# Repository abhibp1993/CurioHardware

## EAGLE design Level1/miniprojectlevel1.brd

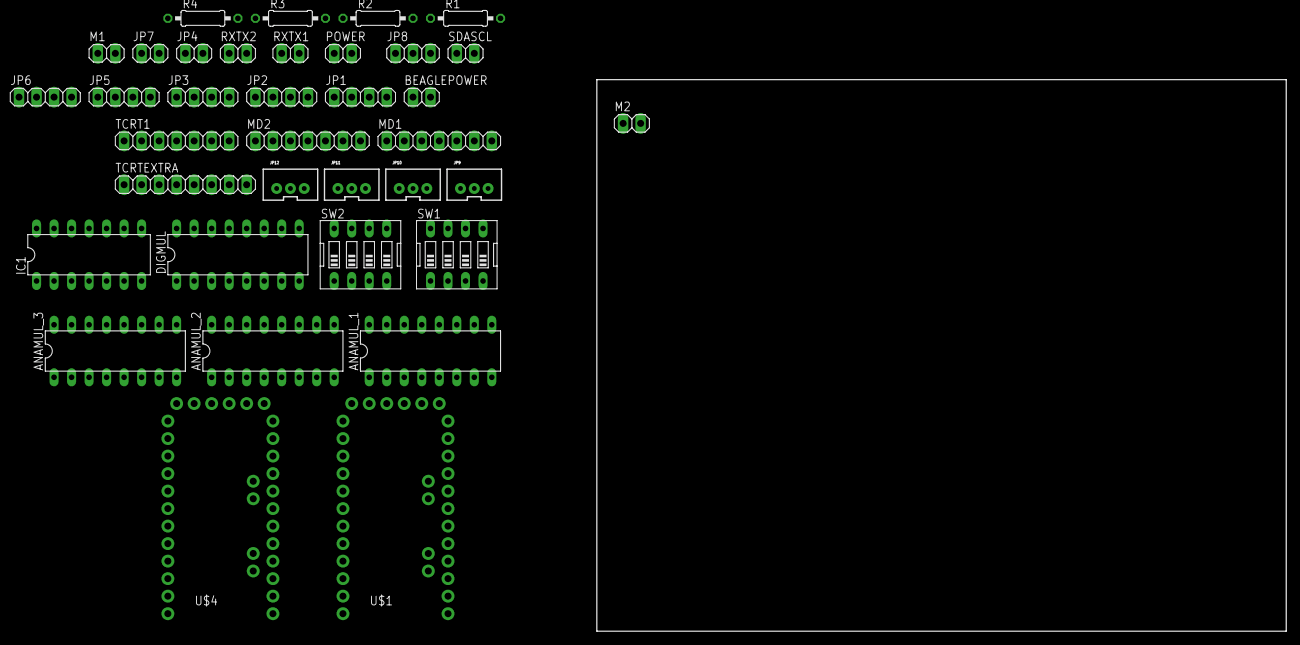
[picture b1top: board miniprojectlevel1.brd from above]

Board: 2 copper layers, 100.0 x 80.0 mm, 36 parts (0 on the bottom side), 64 nets, no tracks yet.

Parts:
ANAMUL_1, ANAMUL_2, ANAMUL_3: 4051N; DIL16
BEAGLEPOWER: 1X02
DIGMUL: 74ACT151N; DIL16
IC1: LM324N; DIL14
JP1, JP2, JP3, JP5, JP6: 1X04
JP4, JP7: 1X02
JP8: 1X03
JP9, JP10, JP11, JP12: JST-3-PTH-VERT
M1, M2: 1X02
MD1, MD2: 1X07
POWER: 1X02
R1, R2, R3, R4: 0207/10
RXTX1, RXTX2: 1X02
SDASCL: 1X02
SW1, SW2: EDG-04
TCRT1: 1X07
TCRTEXTRA: 1X08
U$1, U$4: ARDUINO_PRO_MINI

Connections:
GND: ANAMUL_1.8, ANAMUL_2.8, ANAMUL_3.8, DIGMUL.8
unnamed: DIGMUL.5, U$4.6
unnamed: ANAMUL_1.1, TCRT1.5
unnamed: ANAMUL_1.13, TCRT1.1
unnamed: ANAMUL_1.14, TCRT1.2
unnamed: ANAMUL_1.15, TCRT1.3
unnamed: ANAMUL_1.12, TCRT1.4
unnamed: ANAMUL_1.5, TCRT1.6
unnamed: ANAMUL_1.2, TCRT1.7
unnamed: DIGMUL.2, MD2.3
unnamed: M2.1, U$4.11
unnamed: DIGMUL.4, MD1.3
unnamed: DIGMUL.3, MD1.5
unnamed: DIGMUL.7, DIGMUL.9, JP2.1, JP3.1, JP5.1, JP6.1, JP9.2, JP10.2, JP11.2, JP12.2, MD1.1, MD2.1, R1.1, U$1.4, U$4.4
unnamed: MD1.4, U$4.12
unnamed: DIGMUL.1, MD2.5
unnamed: MD1.2, U$4.14
unnamed: MD1.6, U$4.15
unnamed: MD2.2, U$4.9
unnamed: MD2.6, U$4.8
unnamed: MD2.4, U$4.13
unnamed: ANAMUL_2.13, TCRTEXTRA.8
unnamed: M1.1, U$4.5
unnamed: M1.2, U$4.7
unnamed: M2.2, U$4.10
unnamed: ANAMUL_2.11, SW1.4
unnamed: ANAMUL_2.10, U$4.20
unnamed: ANAMUL_2.3, U$4.19
unnamed: ANAMUL_3.13, JP1.3
unnamed: ANAMUL_3.14, JP2.3
unnamed: R1.2, R4.1
unnamed: ANAMUL_1.11, SW2.4
unnamed: ANAMUL_1.10, U$1.20
unnamed: ANAMUL_1.9, U$1.15
unnamed: ANAMUL_1.3, U$1.A7
unnamed: JP1.2, U$1.5
unnamed: ANAMUL_3.3, U$1.14
unnamed: JP2.2, U$1.6
unnamed: JP3.2, U$1.7
unnamed: JP5.2, U$1.8
unnamed: JP6.2, U$1.9
unnamed: ANAMUL_3.12, JP5.3
unnamed: ANAMUL_3.1, JP6.3
unnamed: R2.2, R3.1
unnamed: ANAMUL_2.15, TCRTEXTRA.6
unnamed: IC1.7, R4.2, U$4.18
unnamed: IC1.1, R3.2, U$4.17
unnamed: ANAMUL_2.12, TCRTEXTRA.5
unnamed: ANAMUL_2.1, TCRTEXTRA.4
unnamed: ANAMUL_2.5, TCRTEXTRA.3
unnamed: ANAMUL_2.2, TCRTEXTRA.2
unnamed: ANAMUL_2.4, TCRTEXTRA.1
unnamed: BEAGLEPOWER.1, SW1.1, SW2.1
unnamed: RXTX2.2, U$1.2
unnamed: BEAGLEPOWER.2, SW1.2, SW2.2
unnamed: SW2.6, SW2.8, U$1.A5
unnamed: SW2.5, SW2.7, U$1.A4
unnamed: SW1.6, U$4.A5
unnamed: JP12.1, U$1.19
unnamed: JP11.1, U$1.18
unnamed: JP10.1, U$1.17
unnamed: JP9.1, U$1.A6
VCC: ANAMUL_1.16, ANAMUL_2.16, ANAMUL_3.16, DIGMUL.16, JP1.4, JP2.4, JP3.4, JP5.4, JP6.4, JP9.3, JP10.3, JP11.3, JP12.3, POWER.1, U$1.21, U$4.21
VEE: ANAMUL_1.7, ANAMUL_2.7, ANAMUL_3.7

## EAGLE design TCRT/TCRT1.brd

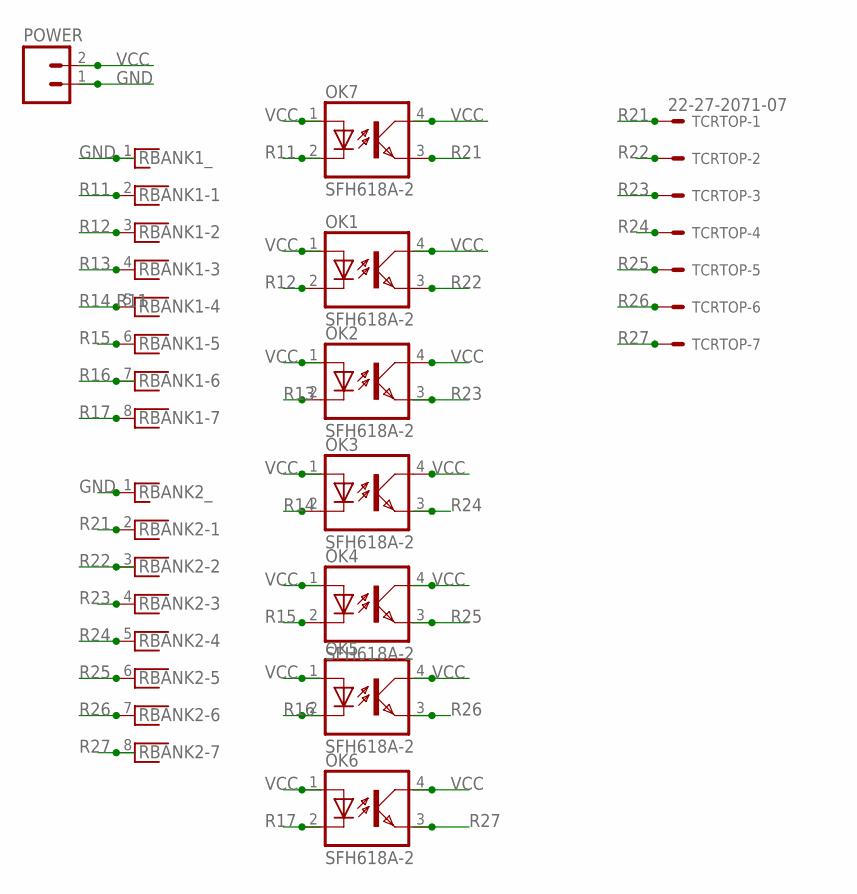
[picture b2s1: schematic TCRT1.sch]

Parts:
OK1, OK2, OK3, OK4, OK5, OK6, OK7: SFH618A-2; DIP4
POWER: M025MM; SCREWTERMINAL-5MM-2
RBANK1, RBANK2: RNX7; RN-8
TCRTOP: 22-27-2071-07; 6410-07

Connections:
GND: POWER.1, RBANK1.1, RBANK2.1
R11: OK7.2 (C), RBANK1.2
R12: OK1.2 (C), RBANK1.3
R13: OK2.2 (C), RBANK1.4
R14: OK3.2 (C), RBANK1.5
R15: OK4.2 (C), RBANK1.6
R16: OK5.2 (C), RBANK1.7
R17: OK6.2 (C), RBANK1.8
R21: OK7.3 (EMIT), RBANK2.2, TCRTOP.1
R22: OK1.3 (EMIT), RBANK2.3, TCRTOP.2
R23: OK2.3 (EMIT), RBANK2.4, TCRTOP.3
R24: OK3.3 (EMIT), RBANK2.5, TCRTOP.4
R25: OK4.3 (EMIT), RBANK2.6, TCRTOP.5
R26: OK5.3 (EMIT), RBANK2.7, TCRTOP.6
R27: OK6.3 (EMIT), RBANK2.8, TCRTOP.7
VCC: OK1.1 (A), OK1.4 (COL), OK2.1 (A), OK2.4 (COL), OK3.1 (A), OK3.4 (COL), OK4.1 (A), OK4.4 (COL), OK5.1 (A), OK5.4 (COL), OK6.1 (A), OK6.4 (COL), OK7.1 (A), OK7.4 (COL), POWER.2

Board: 2 copper layers, 11 parts (5 on the bottom side), 16 nets, no tracks yet.

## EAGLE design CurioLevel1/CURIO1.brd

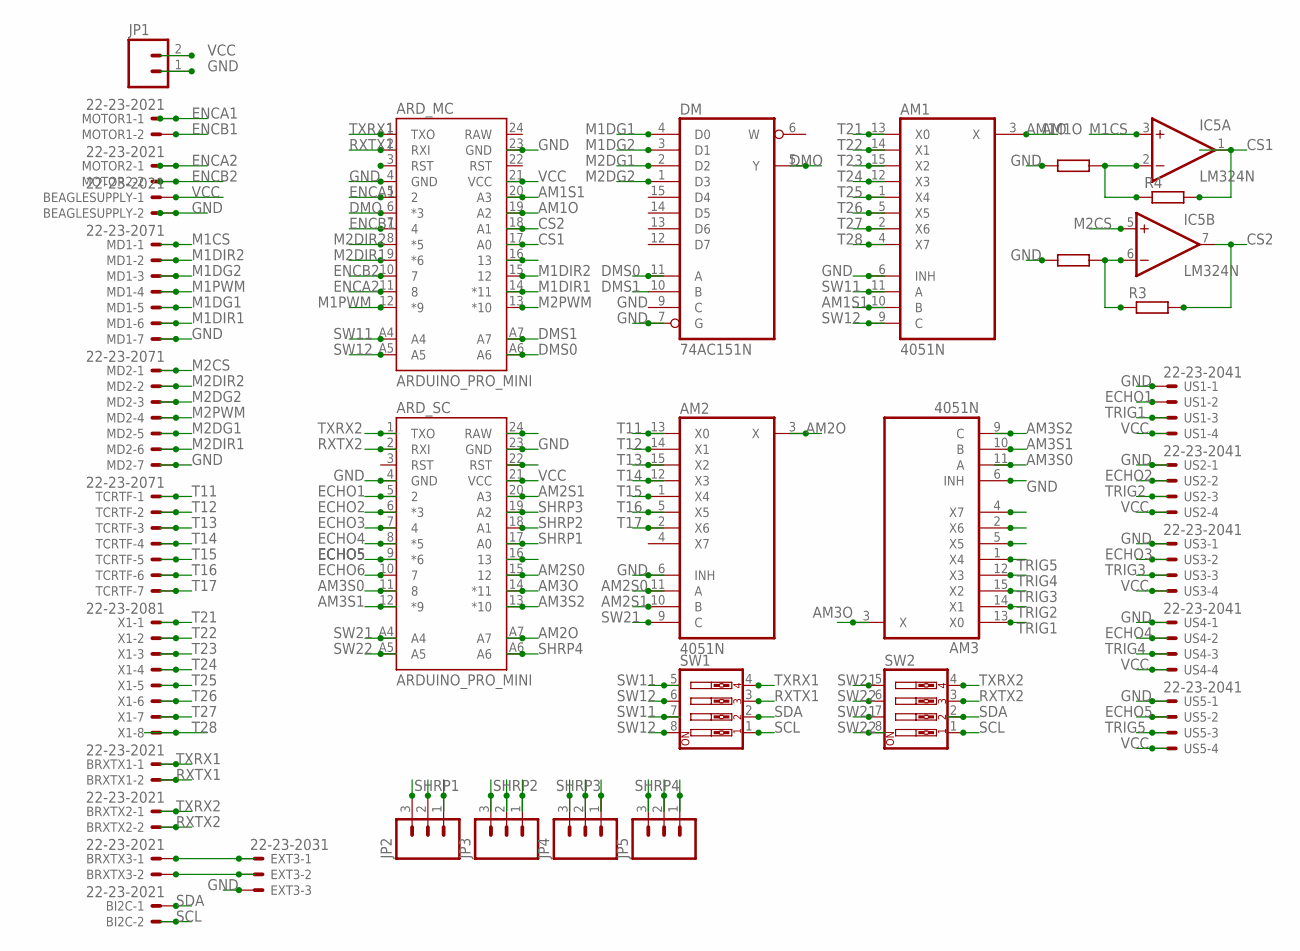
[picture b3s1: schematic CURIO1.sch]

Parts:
AM1, AM2, AM3: 4051N; DIL16
ARD_MC: ARDUINO_PRO_MINI
ARD_SC: ARDUINO_PRO_MINI
BEAGLESUPPLY: 22-23-2021
BI2C: 22-23-2021
BRXTX1, BRXTX2, BRXTX3: 22-23-2021
DM: 74AC151N; DIL16
EXT3: 22-23-2031
IC5: LM324N; DIL14
JP1: M025MM; SCREWTERMINAL-5MM-2
JP2, JP3, JP4, JP5: M03JST-PTH-VERT; JST-3-PTH-VERT
MD1, MD2: 22-23-2071
MOTOR1, MOTOR2: 22-23-2021
R3, R4: R0204/7; 0204/7
SW1, SW2: SW_DIP-4; EDG-04
TCRTF: 22-23-2071
US1, US2, US3, US4, US5: 22-23-2041
X1: 22-23-2081

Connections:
AM1O: AM1.3 (X), ARD_MC.19 (A2)
AM1S1: AM1.10 (B), ARD_MC.20 (A3)
AM2O: AM2.3 (X), ARD_SC.A7
AM2S0: AM2.11 (A), ARD_SC.15 (12)
AM2S1: AM2.10 (B), ARD_SC.20 (A3)
AM3O: AM3.3 (X), ARD_SC.14 (*11)
AM3S0: AM3.11 (A), ARD_SC.11 (8)
AM3S1: AM3.10 (B), ARD_SC.12 (*9)
AM3S2: AM3.9 (C), ARD_SC.13 (*10)
CS1: ARD_MC.17 (A0), IC5.1 (OUT), R4.2
CS2: ARD_MC.18 (A1), IC5.7 (OUT), R3.2
DMO: ARD_MC.6 (*3), DM.5 (Y)
DMS0: ARD_MC.A6, DM.11 (A)
DMS1: ARD_MC.A7, DM.10 (B)
ECHO1: ARD_SC.5 (2), US1.2
ECHO2: ARD_SC.6 (*3), US2.2
ECHO3: ARD_SC.7 (4), US3.2
ECHO4: ARD_SC.8 (*5), US4.2
ECHO5: ARD_SC.9 (*6), US5.2
ECHO6: ARD_SC.10 (7)
ENCA1: ARD_MC.5 (2), MOTOR1.1
ENCA2: ARD_MC.11 (8), MOTOR2.1
ENCB1: ARD_MC.7 (4)
ENCB2: ARD_MC.10 (7), MOTOR2.2
GND: AM1.6 (INH), AM1.8 (GND), AM2.6 (INH), AM2.8 (GND), AM3.6 (INH), AM3.8 (GND), ARD_MC.4 (GND), ARD_MC.23 (GND), ARD_SC.4 (GND), ARD_SC.23 (GND), BEAGLESUPPLY.2, DM.7 (G), DM.8 (GND), EXT3.3, JP1.1, JP2.2, JP3.2, JP4.2, JP5.2, MD1.7, MD2.7, US1.1, US2.1, US3.1, US4.1, US5.1
M1CS: IC5.3 (+IN), MD1.1
M1DG1: DM.4 (D0), MD1.5
M1DG2: DM.3 (D1), MD1.3
M1DIR1: ARD_MC.14 (*11), MD1.6
M1DIR2: ARD_MC.15 (12), MD1.2
M1PWM: ARD_MC.12 (*9), MD1.4
M2CS: IC5.5 (+IN), MD2.1
M2DG1: DM.2 (D2), MD2.5
M2DG2: DM.1 (D3), MD2.3
M2DIR1: ARD_MC.9 (*6), MD2.6
M2DIR2: ARD_MC.8 (*5), MD2.2
M2PWM: ARD_MC.13 (*10), MD2.4
unnamed: BRXTX3.1, EXT3.1
unnamed: BRXTX3.2, EXT3.2
unnamed: IC5.2 (-IN), R4.1
unnamed: IC5.6 (-IN), R3.1
RXTX1: ARD_MC.2 (RXI), BRXTX1.2, SW1.3
RXTX2: ARD_SC.2 (RXI), BRXTX2.2, SW2.3
SCL: BI2C.2, SW1.1, SW2.1
SDA: BI2C.1, SW1.2, SW2.2
SHRP1: ARD_SC.17 (A0), JP2.1
SHRP2: ARD_SC.18 (A1), JP3.1
SHRP3: ARD_SC.19 (A2), JP4.1
SHRP4: ARD_SC.A6, JP5.1
SW11: AM1.11 (A), ARD_MC.A4, SW1.5, SW1.7
SW12: AM1.9 (C), ARD_MC.A5, SW1.6, SW1.8
SW21: AM2.9 (C), ARD_SC.A4, SW2.5, SW2.7
SW22: ARD_SC.A5, SW2.6, SW2.8
T11: AM2.13 (X0), TCRTF.1
T12: AM2.14 (X1), TCRTF.2
T13: AM2.15 (X2), TCRTF.3
T14: AM2.12 (X3), TCRTF.4
T15: AM2.1 (X4), TCRTF.5
T16: AM2.5 (X5), TCRTF.6
T17: AM2.2 (X6), TCRTF.7
T21: AM1.13 (X0), X1.1
T22: AM1.14 (X1), X1.2
T23: AM1.15 (X2), X1.3
T24: AM1.12 (X3), X1.4
T25: AM1.1 (X4), X1.5
T26: AM1.5 (X5), X1.6
T27: AM1.2 (X6), X1.7
T28: AM1.4 (X7), X1.8
TRIG1: AM3.13 (X0), US1.3
TRIG2: AM3.14 (X1), US2.3
TRIG3: AM3.15 (X2), US3.3
TRIG4: AM3.12 (X3), US4.3
TRIG5: AM3.1 (X4), US5.3
TXRX1: ARD_MC.1 (TXO), BRXTX1.1, SW1.4
TXRX2: ARD_SC.1 (TXO), BRXTX2.1, SW2.4
V+: IC5.4 (V+)
V-: IC5.11 (V-)
VCC: AM1.16 (VCC), AM2.16 (VCC), AM3.16 (VCC), ARD_MC.21 (VCC), ARD_SC.21 (VCC), DM.16 (VCC), JP1.2, JP2.3, JP3.3, JP4.3, JP5.3, US1.4, US2.4, US3.4, US4.4, US5.4
VEE: AM1.7 (VEE), AM2.7 (VEE), AM3.7 (VEE)

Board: 2 copper layers, 33 parts (0 on the bottom side), 75 nets, no tracks yet.

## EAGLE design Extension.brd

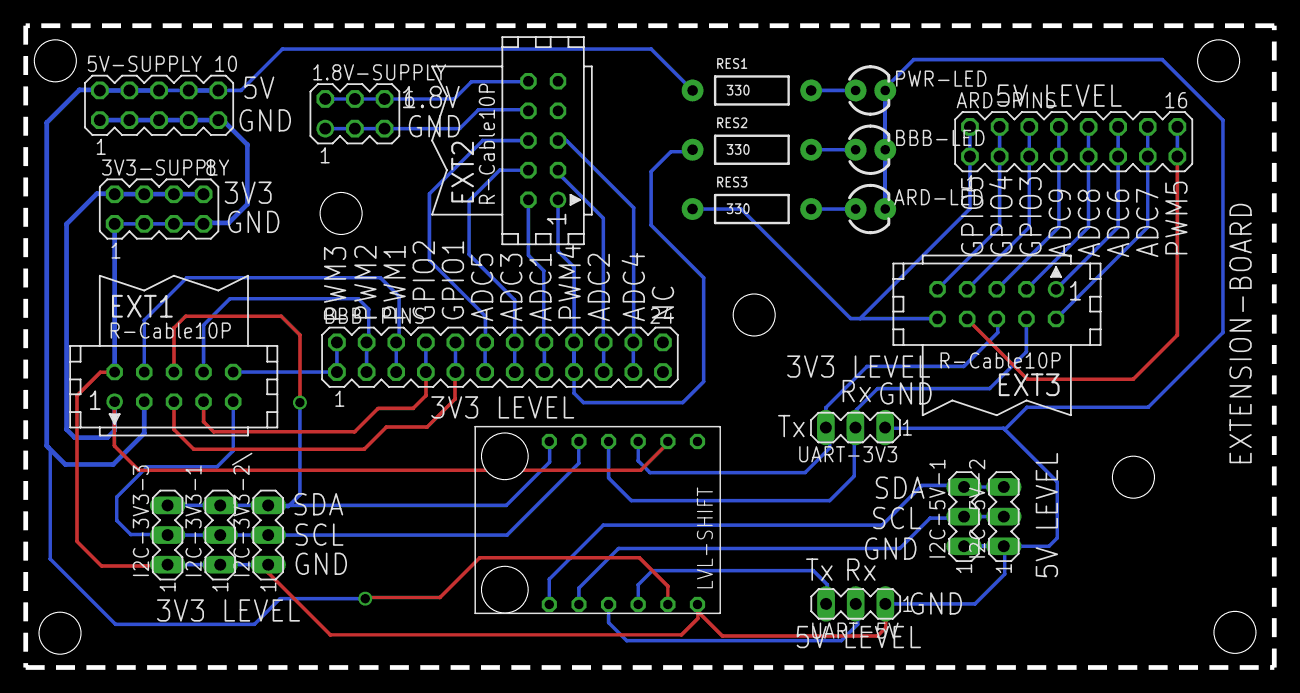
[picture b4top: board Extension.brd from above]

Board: 2 copper layers, 107.0 x 55.0 mm, 22 parts (0 on the bottom side), 35 nets.

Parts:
1.8V-SUPPLY: MA03-2
3V3-SUPPLY: MA04-2
5V-SUPPLY: MA05-2
ARD-LED: Blue; LED3MM
ARD-PINS: MA08-2
BBB-LED: White; LED3MM
BBB-PINS: MA12-2
EXT1, EXT2, EXT3: CON10
I2C-3V3-1, I2C-3V3-2\, I2C-3V3-3, I2C-5V-1, I2C-5V-2: MA03-1
LVL-SHIFT: LEVEL-SHIFTER
PWR-LED: Red; LED3MM
RES1, RES2, RES3: 330; AXIAL-0.4
UART-3V3, UART-5V: MA03-1

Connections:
S$1: EXT1.6, I2C-3V3-1.3, I2C-3V3-2\.3, I2C-3V3-3.3, LVL-SHIFT.P$6
S$2: EXT1.9, I2C-3V3-1.2, I2C-3V3-2\.2, I2C-3V3-3.2, LVL-SHIFT.P$5
S$3: LVL-SHIFT.P$9, UART-5V.3
S$4: EXT3.6, LVL-SHIFT.P$3, UART-3V3.3
S$5: EXT3.4, LVL-SHIFT.P$4, UART-3V3.2
S$6: I2C-5V-1.3, I2C-5V-2.3, LVL-SHIFT.P$12
S$7: I2C-5V-1.2, I2C-5V-2.2, LVL-SHIFT.P$11
S$8: LVL-SHIFT.P$10, UART-5V.2
S$10: 3V3-SUPPLY.2, 3V3-SUPPLY.4, 3V3-SUPPLY.6, 3V3-SUPPLY.8, EXT1.1, LVL-SHIFT.P$2
S$11: 5V-SUPPLY.2, 5V-SUPPLY.4, 5V-SUPPLY.6, 5V-SUPPLY.8, 5V-SUPPLY.10, EXT1.3, LVL-SHIFT.P$8, RES1.P$1
S$12: 1.8V-SUPPLY.1, 1.8V-SUPPLY.3, 1.8V-SUPPLY.5, EXT2.8
S$13: BBB-PINS.1, BBB-PINS.2, EXT1.10
S$14: BBB-PINS.3, BBB-PINS.4, EXT1.8
S$15: BBB-PINS.5, BBB-PINS.6, EXT1.4
S$16: BBB-PINS.7, BBB-PINS.8, EXT1.7
S$17: BBB-PINS.9, BBB-PINS.10, EXT1.5
S$18: BBB-PINS.11, BBB-PINS.12, EXT2.6
S$19: BBB-PINS.13, BBB-PINS.14, EXT2.4
S$20: BBB-PINS.15, BBB-PINS.16, EXT2.2
S$21: BBB-PINS.17, BBB-PINS.18, EXT2.1, RES2.P$1
S$22: BBB-PINS.19, BBB-PINS.20, EXT2.3
S$23: BBB-PINS.21, BBB-PINS.22, EXT2.5
S$24: 1.8V-SUPPLY.2, 1.8V-SUPPLY.4, 1.8V-SUPPLY.6, EXT2.10
S$25: ARD-PINS.15, ARD-PINS.16, EXT3.8
S$26: ARD-PINS.13, ARD-PINS.14, EXT3.2
S$27: ARD-PINS.11, ARD-PINS.12, EXT3.1
S$28: ARD-PINS.9, ARD-PINS.10, EXT3.3
S$29: ARD-PINS.7, ARD-PINS.8, EXT3.5
S$30: ARD-PINS.5, ARD-PINS.6, EXT3.7
S$31: ARD-PINS.3, ARD-PINS.4, EXT3.9
S$32: ARD-PINS.1, ARD-PINS.2, EXT3.10, RES3.P$1
S$33: PWR-LED.A, RES1.P$2
S$34: BBB-LED.A, RES2.P$2
S$35: ARD-LED.A, RES3.P$2
S$36: 3V3-SUPPLY.1, 3V3-SUPPLY.3, 3V3-SUPPLY.5, 3V3-SUPPLY.7, 5V-SUPPLY.1, 5V-SUPPLY.3, 5V-SUPPLY.5, 5V-SUPPLY.7, 5V-SUPPLY.9, ARD-LED.K, BBB-LED.K, EXT1.2, I2C-3V3-1.1, I2C-3V3-2\.1, I2C-3V3-3.1, I2C-5V-1.1, I2C-5V-2.1, LVL-SHIFT.P$7, PWR-LED.K, UART-3V3.1, UART-5V.1

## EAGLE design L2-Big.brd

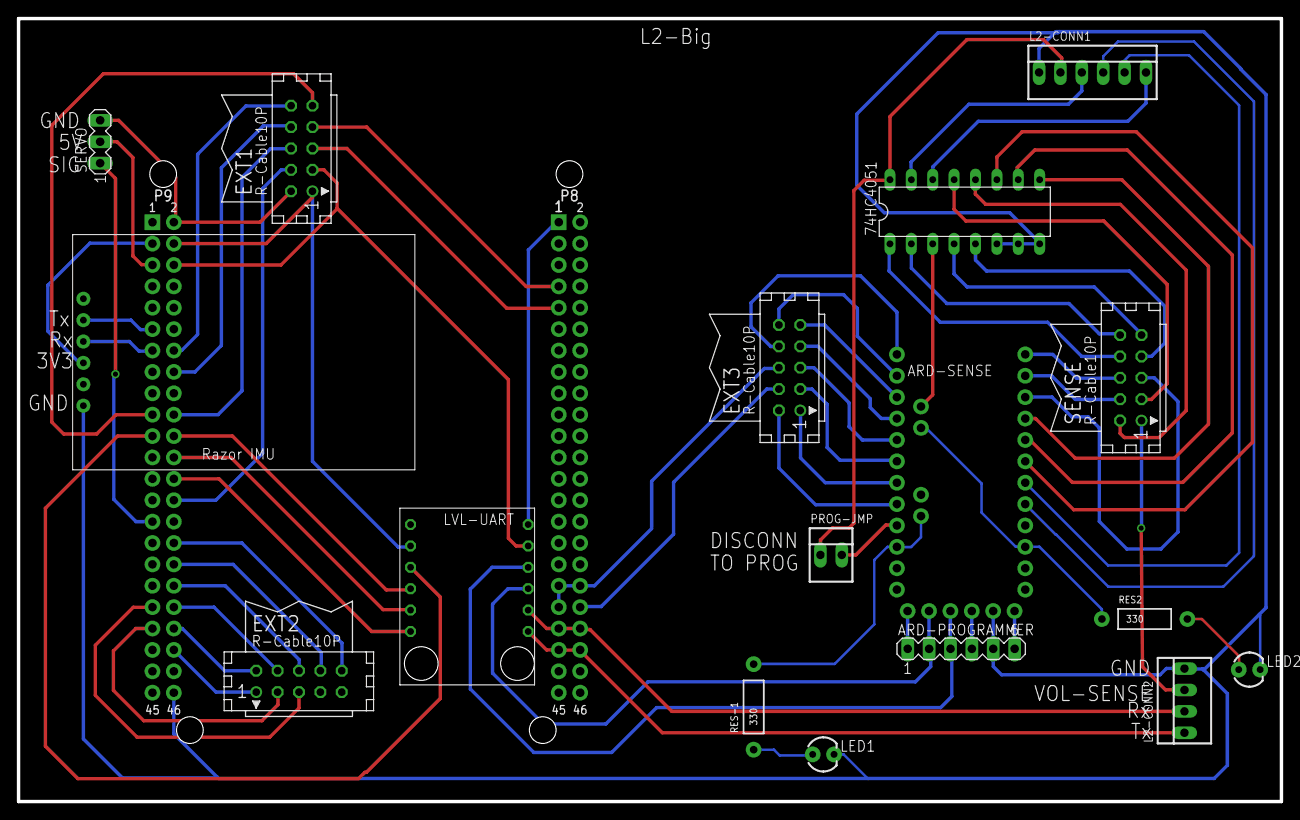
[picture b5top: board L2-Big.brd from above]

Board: 2 copper layers, 150.0 x 93.0 mm, 18 parts (0 on the bottom side), 70 nets.

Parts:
74HC4051: DIL16
ARD-PROGRAMMER: MA06-1
ARD-SENSE: ARDUINO_PRO_MINI
BBB: BEAGLE_BONE_BLACK_CAPE
E$1: RAZOR-IMU
EXT1, EXT2, EXT3: CON10
L2-CONN1: 22-23-2061
L2-CONN2: 22-23-2041
LED1, LED2: Blue; LED3MM
LVL-UART: LEVEL-SHIFTER
PROG-JMP: 22-23-2021
RES2: 330; AXIAL-0.4
RES-1: 330; AXIAL-0.4
SENSE: CON10
SERVO: MA03-1

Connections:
S$1: ARD-SENSE.20, EXT3.2
S$2: ARD-SENSE.19, EXT3.1
S$3: ARD-SENSE.18, EXT3.3
S$4: ARD-SENSE.17, EXT3.5
S$5: L2-CONN2.3, SENSE.1
S$6: 74HC4051.15, L2-CONN1.3
S$7: 74HC4051.16, L2-CONN1.2, PROG-JMP.1
S$8: 74HC4051.14, L2-CONN1.6
S$9: 74HC4051.2, SENSE.10
S$10: 74HC4051.1, SENSE.8
S$11: 74HC4051.4, SENSE.9
S$12: 74HC4051.5, SENSE.7
S$13: 74HC4051.9, ARD-SENSE.9
S$14: 74HC4051.10, ARD-SENSE.8
S$15: 74HC4051.11, ARD-SENSE.7
S$16: ARD-SENSE.11, SENSE.4
S$17: ARD-SENSE.12, SENSE.6
S$18: ARD-SENSE.10, SENSE.5
S$19: 74HC4051.13, SENSE.3
S$20: 74HC4051.12, SENSE.2
S$21: BBB.P9.19, EXT1.9
S$22: ARD-SENSE.16, EXT3.7
S$23: ARD-SENSE.15, EXT3.9
S$24: ARD-SENSE.14, EXT3.10
S$25: ARD-SENSE.13, EXT3.8
S$26: BBB.P9.24, LVL-UART.P$5
S$27: BBB.P9.26, LVL-UART.P$6
S$28: BBB.P8.41, BBB.P8.42, L2-CONN2.1, LVL-UART.P$12
S$29: BBB.P8.39, BBB.P8.40, L2-CONN2.2, LVL-UART.P$11
S$30: BBB.P9.22, LVL-UART.P$4
S$31: BBB.P9.21, LVL-UART.P$3
S$32: 74HC4051.3, ARD-SENSE.A6
S$33: ARD-PROGRAMMER.2, ARD-SENSE.TXO, LVL-UART.P$10
S$34: ARD-PROGRAMMER.3, ARD-SENSE.RXI, LVL-UART.P$9
S$35: BBB.P8.38, EXT3.4
S$36: BBB.P8.35, BBB.P8.36, BBB.P8.37, EXT3.6
S$37: BBB.P8.1, LVL-UART.P$7
S$38: BBB.P9.4, EXT1.1, LVL-UART.P$2
S$39: BBB.P9.6, EXT1.3, LVL-UART.P$8
S$40: BBB.P9.2, EXT1.2, SERVO.3
S$41: BBB.P9.5, SERVO.2
S$42: BBB.P9.14, EXT1.10
S$43: BBB.P9.39, EXT2.3
S$44: BBB.P9.37, EXT2.5
S$45: ARD-SENSE.6, L2-CONN1.5
S$46: ARD-SENSE.5, L2-CONN1.4
S$47: BBB.P9.42, EXT2.1
S$48: BBB.P9.40, EXT2.2
S$49: BBB.P9.38, EXT2.4
S$50: BBB.P9.36, EXT2.6
S$51: BBB.P9.34, EXT2.8
S$52: BBB.P9.32, EXT2.10
S$53: BBB.P9.11, E$1.P$5
S$54: BBB.P9.13, E$1.P$4
S$55: ARD-SENSE.21, PROG-JMP.2
S$56: ARD-SENSE.3, ARD-SENSE.A7, RES2.P$1
S$57: BBB.P9.16, EXT1.8
S$58: BBB.P9.20, EXT1.6
S$59: BBB.P9.28, EXT1.4
S$60: LED2.A, RES2.P$2
S$61: BBB.P8.7, EXT1.7
S$62: BBB.P8.9, EXT1.5
S$63: BBB.P9.29, SERVO.1
S$64: BBB.P9.3, E$1.P$3
S$65: ARD-PROGRAMMER.1, ARD-SENSE.GRN
S$66: ARD-PROGRAMMER.4, ARD-SENSE.VCC
S$67: ARD-PROGRAMMER.6, ARD-SENSE.BLK
S$68: 74HC4051.6, 74HC4051.7, 74HC4051.8, ARD-PROGRAMMER.5, ARD-SENSE.GND, BBB.P9.46, E$1.P$1, L2-CONN1.1, L2-CONN2.4, LED1.K, LED2.K
S$69: ARD-SENSE.22, ARD-SENSE.A5, RES-1.P$2
S$70: LED1.A, RES-1.P$1

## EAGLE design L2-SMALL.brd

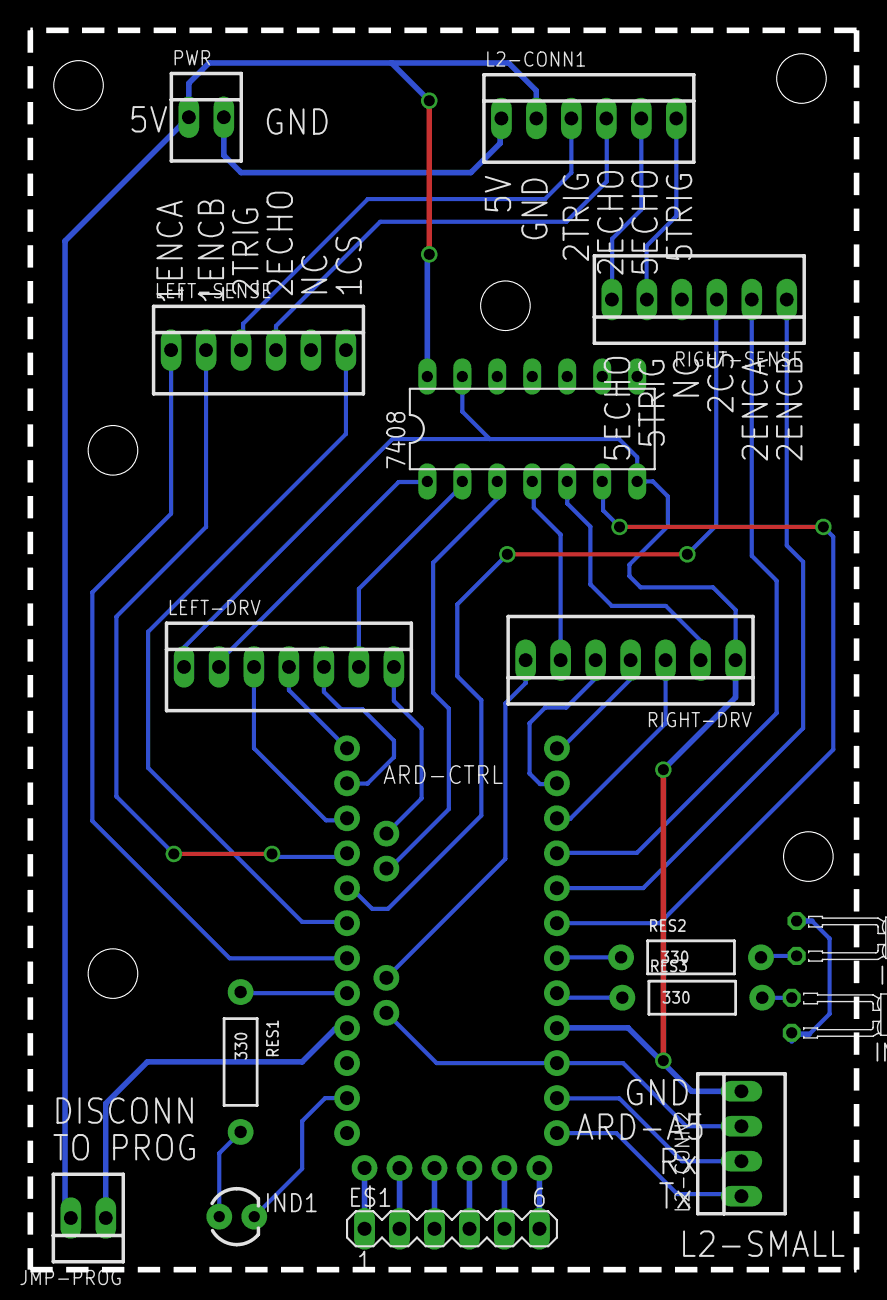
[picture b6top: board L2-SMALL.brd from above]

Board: 2 copper layers, 60.0 x 90.0 mm, 17 parts (0 on the bottom side), 45 nets.

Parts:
7408: DIL14
ARD-CTRL: ARDUINO_PRO_MINI
E$1: MA06-1
IND1: LED3MM
IND2, IND3: LED3MM_H7,5MM
JMP-PROG: 22-23-2021
L2-CONN1: female berg; 22-23-2061
L2-CONN2: female berg; 22-23-2041
LEFT-DRV: 22-23-2071
LEFT-SENSE: 22-23-2061
PWR: 22-23-2021
RES1, RES2, RES3: 330; AXIAL-0.4
RIGHT-DRV: 22-23-2071
RIGHT-SENSE: 22-23-2061

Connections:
S$1: ARD-CTRL.A6, LEFT-DRV.7
S$2: 7408.14, JMP-PROG.2, L2-CONN1.2, PWR.1
S$3: ARD-CTRL.10, RIGHT-DRV.3
S$4: ARD-CTRL.12, RIGHT-DRV.4
S$5: ARD-CTRL.11, RIGHT-DRV.5
S$6: ARD-CTRL.9, RIGHT-SENSE.2
S$7: 7408.3, ARD-CTRL.A7
S$8: ARD-CTRL.13, LEFT-DRV.4
S$9: 7408.6, ARD-CTRL.7
S$10: ARD-CTRL.14, LEFT-DRV.5
S$11: L2-CONN1.4, LEFT-SENSE.4
S$12: 7408.1, LEFT-DRV.2
S$13: 7408.2, LEFT-DRV.6
S$14: 7408.4, RIGHT-DRV.6
S$15: 7408.5, RIGHT-DRV.2
S$16: ARD-CTRL.15, LEFT-DRV.3
S$17: ARD-CTRL.19, LEFT-SENSE.1
S$18: ARD-CTRL.16, LEFT-SENSE.2
S$19: ARD-CTRL.18, LEFT-SENSE.6
S$20: ARD-CTRL.17, RIGHT-SENSE.3
S$21: ARD-CTRL.BLK, E$1.6
S$22: ARD-CTRL.GND, E$1.5
S$23: ARD-CTRL.VCC, E$1.4
S$24: ARD-CTRL.RXI, E$1.3
S$25: ARD-CTRL.TXO, E$1.2
S$26: ARD-CTRL.GRN, E$1.1
S$27: ARD-CTRL.A4, RIGHT-DRV.7
S$28: ARD-CTRL.8, RIGHT-SENSE.1
S$29: L2-CONN1.1, PWR.2
S$30: L2-CONN1.3, LEFT-SENSE.3
S$31: L2-CONN1.6, RIGHT-SENSE.5
S$32: L2-CONN1.5, RIGHT-SENSE.6
S$33: IND2.A, IND3.K
S$34: ARD-CTRL.21, JMP-PROG.1
S$35: ARD-CTRL.1, L2-CONN2.1
S$36: ARD-CTRL.2, L2-CONN2.2
S$37: ARD-CTRL.A5, L2-CONN2.3
S$38: ARD-CTRL.20, RES1.P$1
S$39: IND1.A, RES1.P$2
S$40: ARD-CTRL.23, IND1.K
S$41: ARD-CTRL.6, RES2.P$1
S$42: ARD-CTRL.5, RES3.P$1
S$43: IND2.K, RES2.P$2
S$44: IND3.A, RES3.P$2
S$45: 7408.7, 7408.13, ARD-CTRL.4, L2-CONN2.4, LEFT-DRV.1, RIGHT-DRV.1

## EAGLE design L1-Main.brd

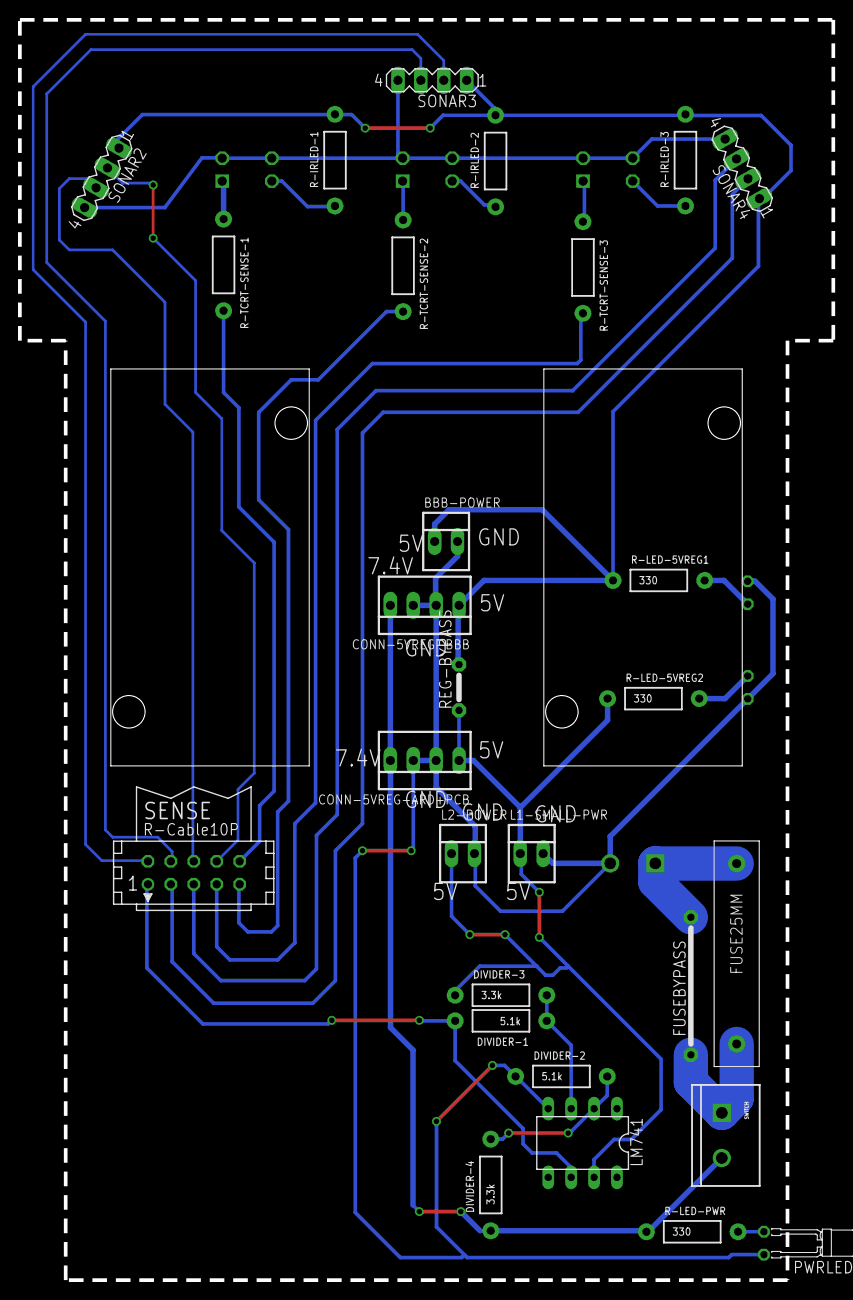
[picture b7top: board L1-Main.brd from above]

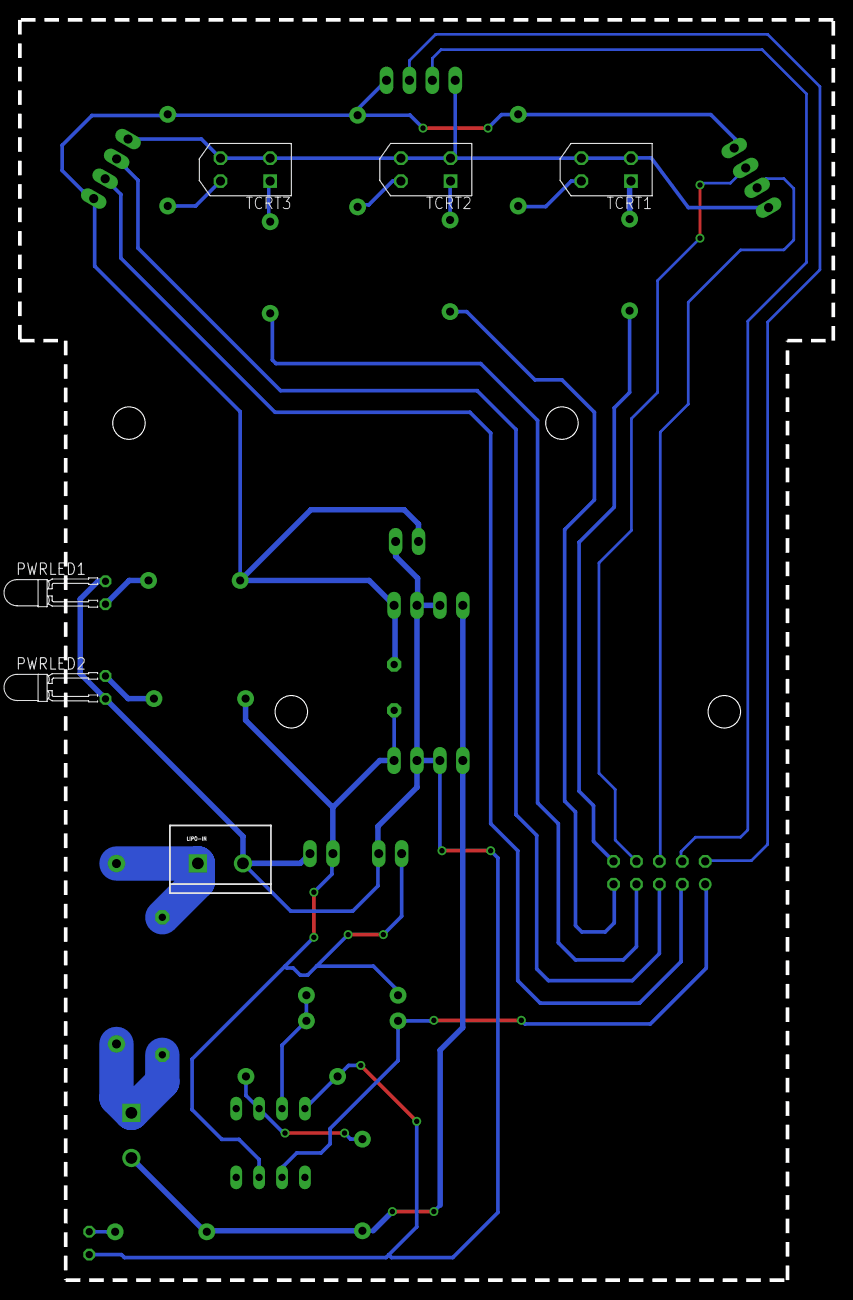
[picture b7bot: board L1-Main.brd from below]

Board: 2 copper layers, 90.2 x 139.7 mm, 36 parts (6 on the bottom side), 28 nets.

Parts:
5VREG-BBB: 5V3A_REG
BBB-POWER: 22-23-2021
CONN-5VREG-ARD+PCB, CONN-5VREG-BBB: 22-23-2041
DIVIDER-1, DIVIDER-2: 5.1k; AXIAL-0.4
DIVIDER-3, DIVIDER-4: 3.3k; AXIAL-0.4
FUSEBYPASS: 15
L1-SMALL-PWR: 5V; 22-23-2021
L2-POWER: 22-23-2021
LIPO-IN: SCREWTERMINAL-5MM-2
LM741: DIL08
PWR-SW: FUSE25MM
PWRLED: green; LED3MM_H7,5MM
PWRLED1, PWRLED2: yellow; LED3MM_H7,5MM
R-IRLED-1, R-IRLED-2, R-IRLED-3: AXIAL-0.4
R-LED-5VREG1, R-LED-5VREG2: 330; AXIAL-0.4
R-LED-PWR: 330; AXIAL-0.4
R-TCRT-SENSE-1, R-TCRT-SENSE-2, R-TCRT-SENSE-3: AXIAL-0.4
REG-BYPASS: 05
REG_ARD+PCB: 5V3A_REG
SENSE: CON10
SONAR2, SONAR3, SONAR4: MA04-1
SWITCH: SCREWTERMINAL-5MM-2
TCRT1, TCRT2, TCRT3: TCRT

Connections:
S$1: FUSEBYPASS.2, LIPO-IN.1, PWR-SW.PIN2
S$2: FUSEBYPASS.1, PWR-SW.PIN1, SWITCH.1
S$4: PWRLED.A, R-LED-PWR.P$2
S$5: R-IRLED-1.P$1, TCRT1.LED-VCC
S$6: CONN-5VREG-ARD+PCB.4, CONN-5VREG-BBB.4, DIVIDER-4.P$1, R-LED-PWR.P$1, SWITCH.2
S$7: R-TCRT-SENSE-1.P$1, TCRT1.COLLECTOR
S$8: PWRLED1.A, R-LED-5VREG1.P$2
S$9: PWRLED2.K, R-LED-5VREG2.P$2
S$10: SENSE.3, SONAR4.2
S$11: CONN-5VREG-ARD+PCB.1, DIVIDER-3.P$1, L1-SMALL-PWR.1, L2-POWER.1, LM741.7, R-LED-5VREG2.P$1, REG-BYPASS.1
S$12: SONAR2.4, SONAR3.4, SONAR4.4, TCRT1.EMITTER, TCRT1.LED-GND, TCRT2.EMITTER, TCRT2.LED-GND, TCRT3.EMITTER, TCRT3.LED-GND
S$13: R-TCRT-SENSE-2.P$1, TCRT2.COLLECTOR
S$14: DIVIDER-1.P$1, DIVIDER-3.P$2, LM741.3
S$15: DIVIDER-2.P$2, DIVIDER-4.P$2, LM741.2
S$16: DIVIDER-1.P$2, LM741.6, SENSE.1
S$17: BBB-POWER.2, CONN-5VREG-ARD+PCB.2, CONN-5VREG-ARD+PCB.3, CONN-5VREG-BBB.2, CONN-5VREG-BBB.3, DIVIDER-2.P$1, L1-SMALL-PWR.2, L2-POWER.2, LIPO-IN.2, LM741.4, PWRLED.K, PWRLED1.K, PWRLED2.A
S$18: R-IRLED-2.P$1, TCRT2.LED-VCC
S$19: R-TCRT-SENSE-3.P$1, TCRT3.COLLECTOR
S$20: R-IRLED-3.P$1, TCRT3.LED-VCC
S$21: SENSE.5, SONAR4.3
S$22: SENSE.6, SONAR2.3
S$23: SENSE.8, SONAR2.2
S$24: SENSE.4, SONAR3.3
S$25: SENSE.2, SONAR3.2
S$26: R-TCRT-SENSE-3.P$2, SENSE.7
S$27: R-TCRT-SENSE-2.P$2, SENSE.9
S$28: R-TCRT-SENSE-1.P$2, SENSE.10
S$29: BBB-POWER.1, CONN-5VREG-BBB.1, R-IRLED-1.P$2, R-IRLED-2.P$2, R-IRLED-3.P$2, R-LED-5VREG1.P$1, REG-BYPASS.2, SONAR2.1, SONAR3.1, SONAR4.1

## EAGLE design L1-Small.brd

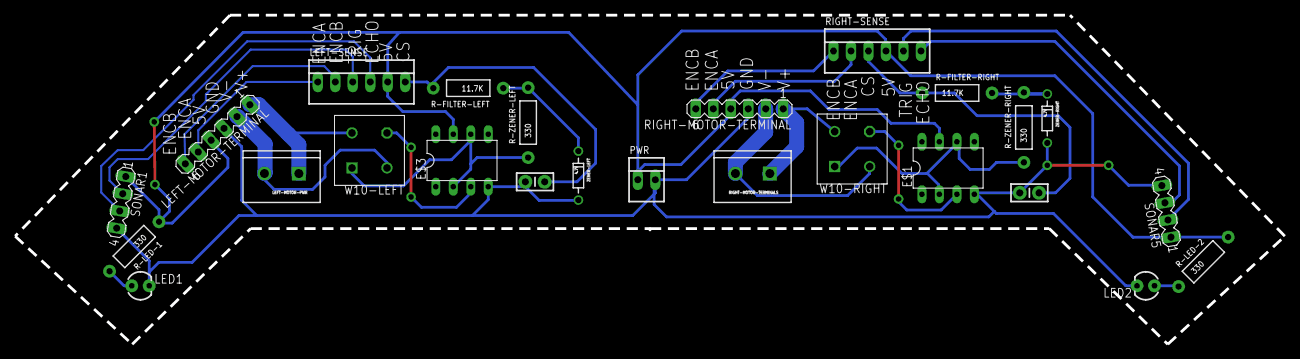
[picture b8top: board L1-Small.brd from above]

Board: 2 copper layers, 184.4 x 47.8 mm, 25 parts (0 on the bottom side), 24 nets.

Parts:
CAP-LEFT: 100uF; CAP-PTH-SMALL-KIT
CAP-RIGHT: 100uF; CAP-PTH-SMALL-KIT
E$1, E$3: DIL08
LED1, LED2: Blue; LED3MM
LEFT-MOTOR-PWR: SCREWTERMINAL-5MM-2
LEFT-MOTOR-TERMINAL: MA06-1
LEFT-SENSE: 22-23-2061
PWR: 5V; 22-23-2021
R-FILTER-LEFT: 11.7K; AXIAL-0.4
R-FILTER-RIGHT: 11.7K; AXIAL-0.4
R-LED-1, R-LED-2: 330; AXIAL-0.4
R-ZENER-LEFT: 330; AXIAL-0.4
R-ZENER-RIGHT: 330; AXIAL-0.4
RIGHT-MOTOR-TERMINAL: MA06-1
RIGHT-MOTOR-TERMINALS: SCREWTERMINAL-5MM-2
RIGHT-SENSE: 22-23-2061
SONAR1, SONAR5: MA04-1
W10-LEFT, W10-RIGHT: W10
ZENER-LEFT: 4.7V; DIODE-ZENER
ZENER-RIGHT: 4.7V; DIODE-ZENER

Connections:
S$2: CAP-LEFT.2, CAP-RIGHT.2, E$1.4, E$3.4, LED1.K, LED2.K, LEFT-MOTOR-TERMINAL.3, PWR.2, RIGHT-MOTOR-TERMINAL.3, SONAR1.4, SONAR5.4, ZENER-LEFT.P$2, ZENER-RIGHT.P$2
S$3: LEFT-MOTOR-PWR.1, LEFT-MOTOR-TERMINAL.1, W10-LEFT.AC2
S$4: LEFT-MOTOR-PWR.2, LEFT-MOTOR-TERMINAL.2, W10-LEFT.AC1
S$5: RIGHT-MOTOR-TERMINAL.2, RIGHT-MOTOR-TERMINALS.2, W10-RIGHT.AC1
S$6: RIGHT-MOTOR-TERMINAL.1, RIGHT-MOTOR-TERMINALS.1, W10-RIGHT.AC2
S$7: E$3.2, E$3.6, R-ZENER-LEFT.P$1, W10-LEFT.VCC+
S$8: E$1.2, E$1.6, R-ZENER-RIGHT.P$1, W10-RIGHT.VCC+
S$9: LED1.A, R-LED-1.P$2
S$10: E$3.3, W10-LEFT.GND
S$11: E$1.3, W10-RIGHT.GND
S$12: R-FILTER-LEFT.P$1, R-ZENER-LEFT.P$2, ZENER-LEFT.P$1
S$13: CAP-LEFT.1, LEFT-SENSE.6, R-FILTER-LEFT.P$2
S$14: R-FILTER-RIGHT.P$2, R-ZENER-RIGHT.P$2, ZENER-RIGHT.P$1
S$15: CAP-RIGHT.1, R-FILTER-RIGHT.P$1, RIGHT-SENSE.3
S$16: LED2.A, R-LED-2.P$1
S$17: LEFT-SENSE.4, SONAR1.3
S$18: LEFT-SENSE.3, SONAR1.2
S$19: LEFT-MOTOR-TERMINAL.6, LEFT-SENSE.2
S$20: LEFT-MOTOR-TERMINAL.5, LEFT-SENSE.1
S$21: E$1.7, E$3.7, LEFT-MOTOR-TERMINAL.4, LEFT-SENSE.5, PWR.1, R-LED-1.P$1, R-LED-2.P$2, RIGHT-MOTOR-TERMINAL.4, RIGHT-SENSE.4, SONAR1.1, SONAR5.1
S$22: RIGHT-MOTOR-TERMINAL.5, RIGHT-SENSE.2
S$23: RIGHT-MOTOR-TERMINAL.6, RIGHT-SENSE.1
S$24: RIGHT-SENSE.6, SONAR5.3
S$25: RIGHT-SENSE.5, SONAR5.2

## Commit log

2015-10-22 Initial Commit...
2015-10-22 All boards defined
2015-10-27 L1 RIGHT AND LEFT MERGED .FINAL CHECKING REMAINS
2015-10-29 L2 Small Board done
2015-12-17 redesigned all boards.

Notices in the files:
parts and their libraries:
SparkFun-Boards: Licensing: Creative Commons ShareAlike 4.0 International - https://creativecommons.org/licenses/by-sa/4.0
